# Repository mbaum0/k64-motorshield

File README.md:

# k64-motorshield
nxp k64 shield to adapt to a raspberry pi motorshield

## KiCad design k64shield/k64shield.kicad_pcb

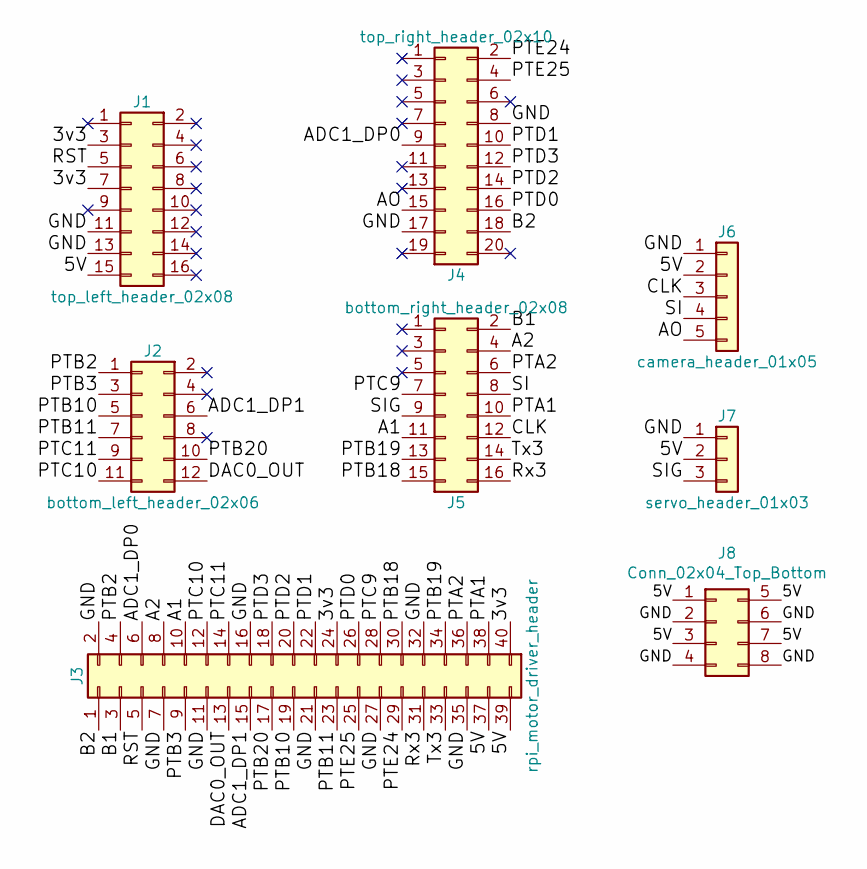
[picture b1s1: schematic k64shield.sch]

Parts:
J1: top_left_header_02x08; Pin_Header_Straight_2x08_Pitch2.54mm
J2: bottom_left_header_02x06; Pin_Header_Straight_2x06_Pitch2.54mm
J3: rpi_motor_driver_header; Pin_Header_Straight_2x20_Pitch2.54mm
J4: top_right_header_02x10; Pin_Header_Straight_2x10_Pitch2.54mm
J5: bottom_right_header_02x08; Pin_Header_Straight_2x08_Pitch2.54mm
J6: camera_header_01x05; Pin_Header_Straight_1x05_Pitch2.54mm
J7: servo_header_01x03; Pin_Header_Straight_1x03_Pitch2.54mm
J8: Conn_02x04_Top_Bottom; Pin_Header_Straight_2x04_Pitch2.54mm

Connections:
/3v3: J1.3 (NC-3), J1.7 (NC-7), J3.24 (CE0-24), J3.40 (P29-40)
/5V: J1.15 (NC-15), J3.37 (P25-37), J3.39 (GND-39), J6.2 (VDD), J7.2 (VDD), J8.1, J8.3, J8.5, J8.7
/A1: J3.10 (RX-10), J5.11 (PTC0-11)
/A2: J3.8 (TX-8), J5.4 (PTC17-4)
/ADC1_DP0: J3.6 (GND-6), J4.9 (NC-9)
/ADC1_DP1: J2.6 (PTB10-6), J3.15 (P3-15)
/AO: J4.15 (NC-15), J6.5 (AO)
/B1: J3.3 (SDA-3), J5.2 (PTC16-2)
/B2: J3.1 (3v3-1), J4.18 (PTE25-18)
/CLK: J5.12 (PTA2-12), J6.3 (CLK)
/DAC0_OUT: J2.12 (PTC10-12), J3.13 (P2-13)
/GND: J1.11 (NC-11), J1.13 (NC-13), J3.2 (5v-2), J3.7 (P7-7), J3.11 (P0-11), J3.16 (P4-16), J3.21 (MISO-21), J3.27 (IDSO-27), J3.32 (P26-32), J3.35 (P24-35), J4.8 (PTD2-8), J4.17 (ADC1_SE18-17), J6.1 (GND), J7.1 (GND), J8.2, J8.4, J8.6, J8.8
/PTA1: J3.38 (P28-38), J5.10 (PTB23-10)
/PTA2: J3.36 (P27-36), J5.6 (PTB9-6)
/PTB2: J2.1 (ADC0_DP1-1), J3.4 (5v-4)
/PTB3: J2.3 (ADC0_DM1-3), J3.9 (GND-9)
/PTB10: J2.5 (ADC1_DP1-5), J3.19 (MOSI-19)
/PTB11: J2.7 (ADC1_DM1-7), J3.23 (SCK-23)
/PTB18: J3.30 (GND-30), J5.15 (PTC5-15)
/PTB19: J3.34 (GND-34), J5.13 (PTC7-13)
/PTB20: J2.10 (PTC11-10), J3.17 (3v3-17)
/PTC9: J3.28 (IDSC-28), J5.7 (PTC8-7)
/PTC10: J2.11 (DAC0_OUT-11), J3.12 (P1-12)
/PTC11: J2.9 (PTB20-9), J3.14 (GND-14)
/PTD0: J3.26 (CE1-26), J4.16 (AREF-16)
/PTD1: J3.22 (P6-22), J4.10 (PTD3-10)
/PTD2: J3.20 (GND-20), J4.14 (GND-14)
/PTD3: J3.18 (P5-18), J4.12 (PTD1-12)
/PTE24: J3.29 (P21-29), J4.2 (PTC12-2)
/PTE25: J3.25 (GND-25), J4.4 (PTC4-4)
/RST: J1.5 (NC-5), J3.5 (SCL-5)
/Rx3: J3.31 (P22-31), J5.16 (PTC3-16)
/SI: J5.8 (PTA1-8), J6.4 (SI)
/SIG: J5.9 (PTC9-9), J7.3 (SIG)
/Tx3: J3.33 (P23-33), J5.14 (PTC2-14)

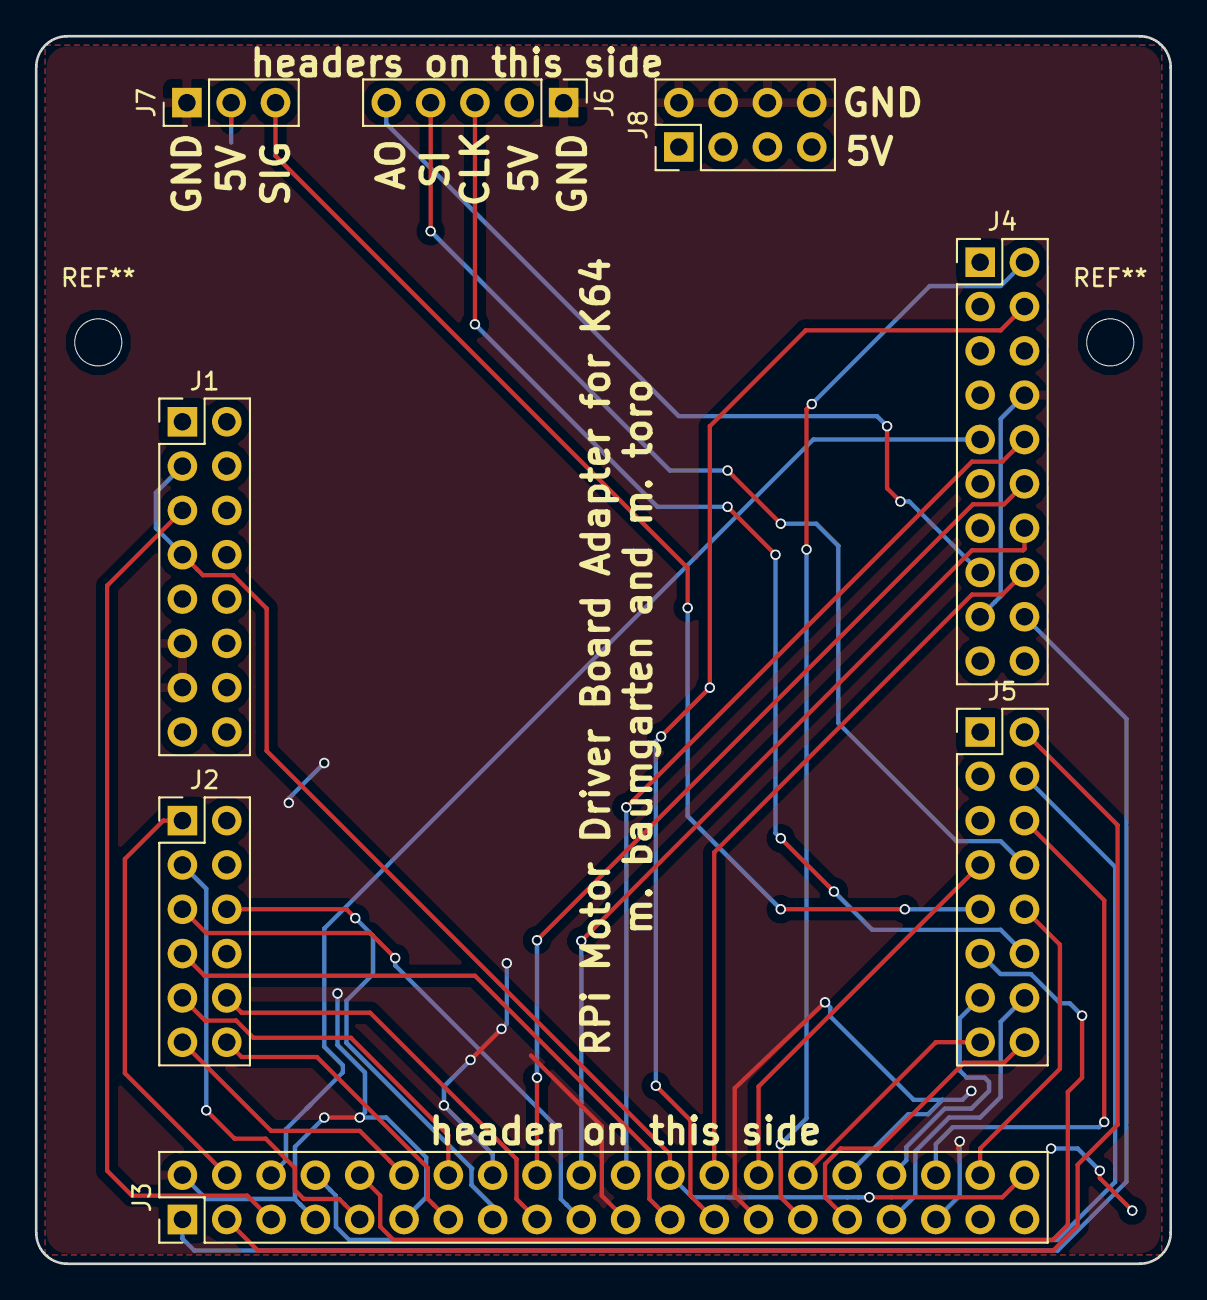
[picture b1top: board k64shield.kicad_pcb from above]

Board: 2 copper layers, 65.0 x 70.4 mm, 8 parts (0 on the bottom side), 35 nets.

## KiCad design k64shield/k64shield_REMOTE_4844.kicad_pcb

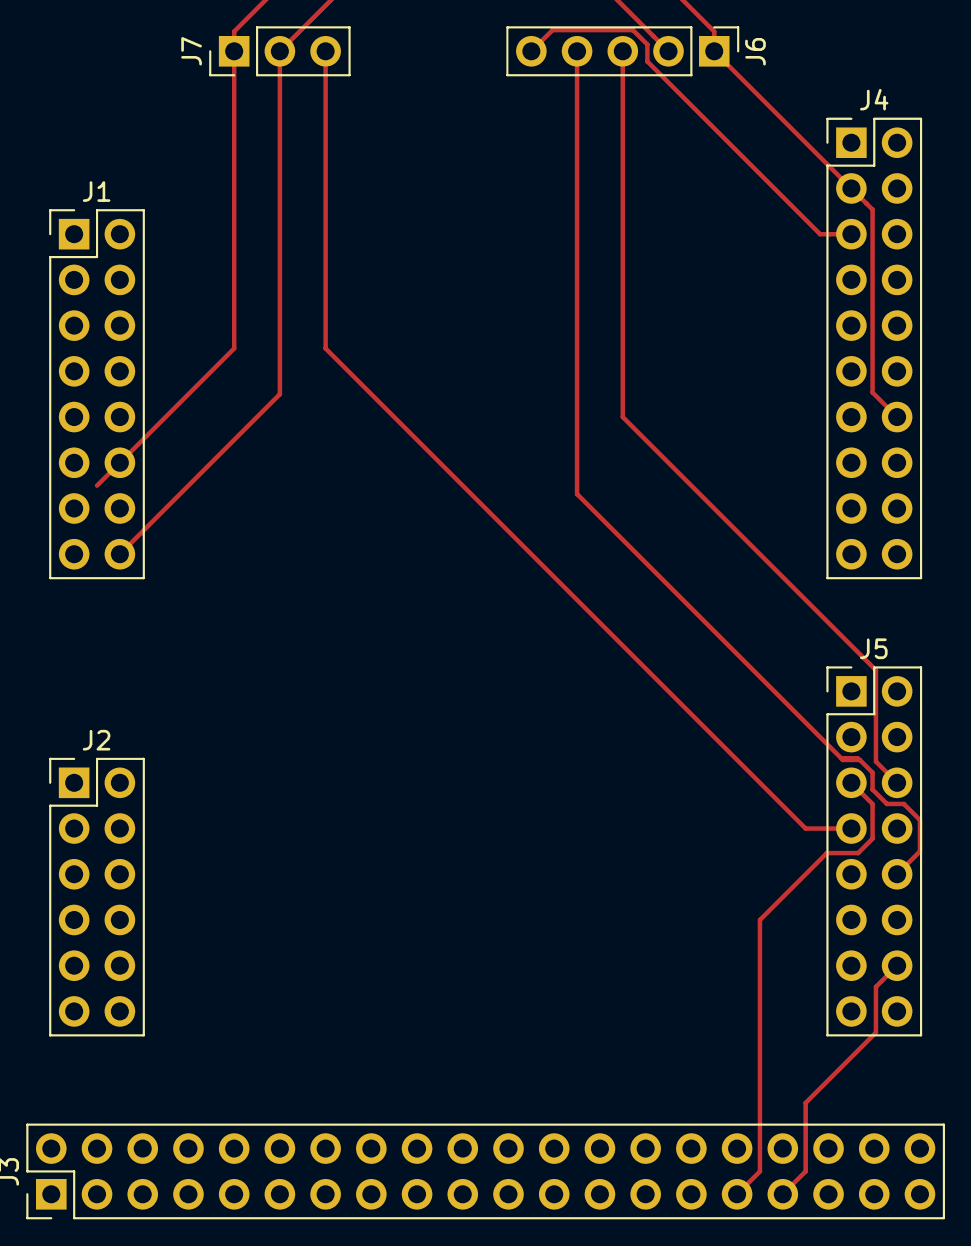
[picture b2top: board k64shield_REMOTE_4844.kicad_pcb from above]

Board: 2 copper layers, 7 parts (0 on the bottom side), 10 nets.

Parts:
J1: top_left_header_02x08; Pin_Header_Straight_2x08_Pitch2.54mm
J2: bottom_left_header_02x06; Pin_Header_Straight_2x06_Pitch2.54mm
J3: rpi_motor_driver_header; Pin_Header_Straight_2x20_Pitch2.54mm
J4: top_right_header_02x10; Pin_Header_Straight_2x10_Pitch2.54mm
J5: bottom_right_header_02x08; Pin_Header_Straight_2x08_Pitch2.54mm
J6: camera_header_01x05; Pin_Header_Straight_1x05_Pitch2.54mm
J7: servo_header_01x03; Pin_Header_Straight_1x03_Pitch2.54mm

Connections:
/5V: J1.16, J3.2, J3.4, J6.2, J7.2
/A1: J3.31, J5.5
/A2: J3.33, J5.14
/AO: J4.5, J6.5
/B1: J3.38, J5.16
/B2: J3.40, J4.4
/CLK: J5.6, J6.3
/GND: J1.12, J1.14, J3.6, J3.9, J3.14, J3.20, J3.25, J3.30, J3.34, J3.39, J4.3, J4.14, J6.1, J7.1
/SI: J5.10, J6.4
/SIG: J5.7, J7.3

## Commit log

2018-11-14 Init project
2018-11-15 Some of the PCB completed
2018-11-18 Saving so I have a point to revert to - pins are very messed up
2018-11-19 Fixed all wiring. Everything is connected on PCB
2018-11-19 2nd working commit
2018-11-19 Working project
2018-11-19 Working
2018-11-19 Finished reroute
2018-11-19 added title and names to silk screen
2018-11-19 moved pins so enable were connected to gpio
